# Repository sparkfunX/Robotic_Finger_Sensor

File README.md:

Robotic Finger Sensor 
========================

[*Robotic Finger Sensor (SPX-14200)*](https://www.sparkfun.com/products/14200)  

[*Robotic Finger Sensor v2 (SPX-14687)*](https://www.sparkfun.com/products/14687)

A robotic finger sensor capable of detecting very light touches. Uses the VCNL4040 IR distance sensor. 

Repository Contents
------------------

* **/Firmware** - Example Arduino sketch to demostrate how to read from the various sensors.
* **/Hardware** - All the Eagle PCB design files (.brd, .sch). MOld files are included as well. 

License Information
-------------------

This product is _**open source**_! 

Please review the LICENSE.md file for license information. 

If you have any questions or concerns on licensing, please contact technical support on our [SparkFun forums](https://forum.sparkfun.com/viewforum.php?f=152).

Distributed as-is; no warranty is given.

- Your friends at SparkFun.

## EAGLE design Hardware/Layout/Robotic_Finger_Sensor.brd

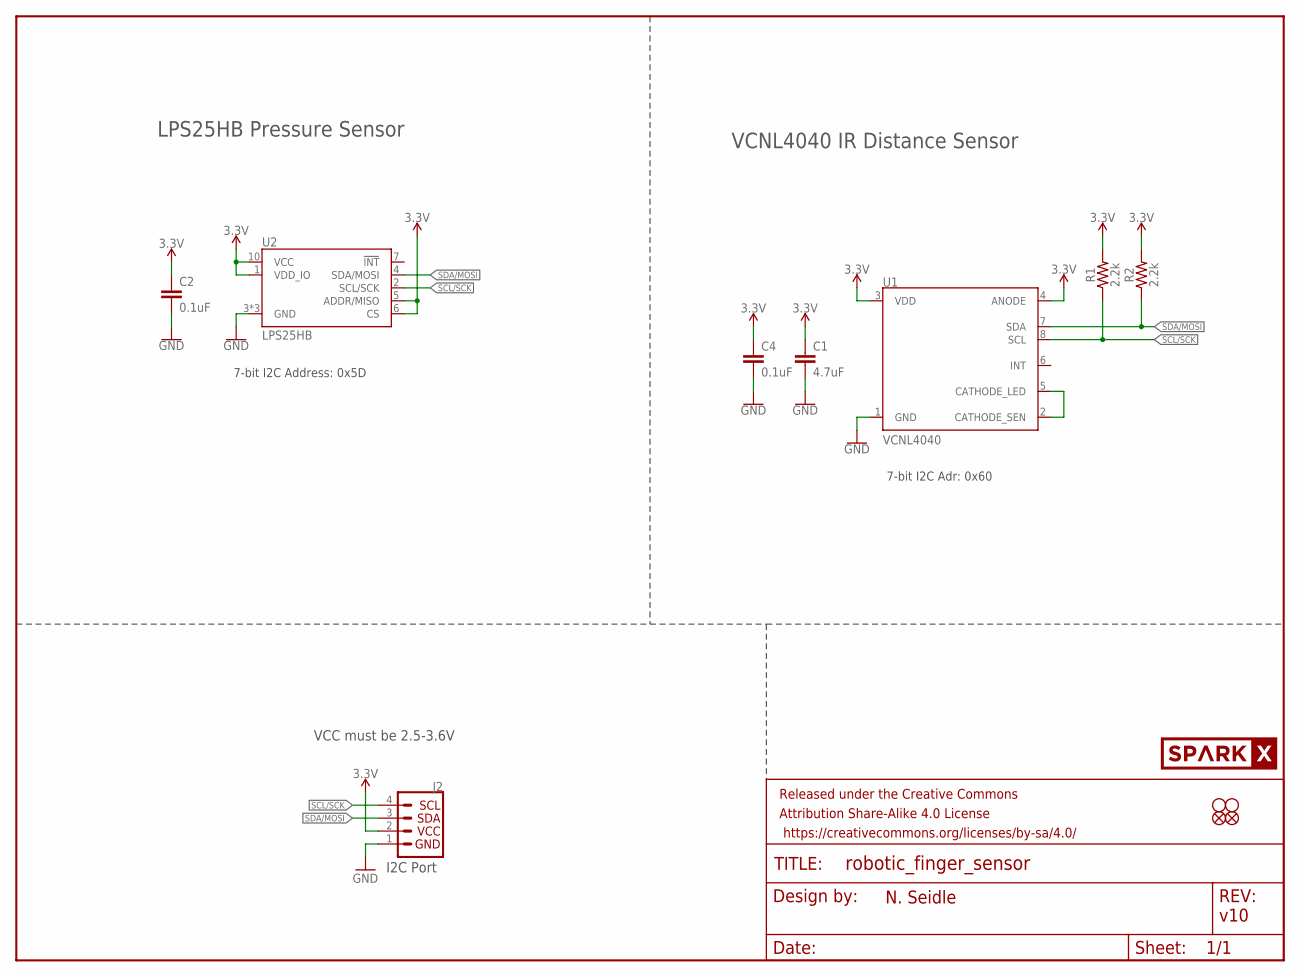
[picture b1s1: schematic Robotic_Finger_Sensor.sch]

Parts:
C1: 4.7uF; 0603
C2, C4: 0.1uF; 0603
FD1, FD2: FIDUCIALUFIDUCIAL; FIDUCIAL-MICRO
FRAME2: FRAME-LETTER; CREATIVE_COMMONS
J2: I2C_STANDARDJS-1MM; 1X04_1MM_RA
R1, R2: 2.2k; 0603
U1: VCNL4040
U2: LPS25HB
U$2: SPARKX-LOGO3; SPARKX-SMALL
U$3, U$4: STAND-OFF; STAND-OFF-#2

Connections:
3.3V: C1.1, C2.1, C4.1, J2.2 (VCC), R1.2, R2.2, U1.3 (VDD), U1.4 (ANODE), U2.1 (VDD_IO), U2.5 (ADDR/MISO), U2.6 (CS), U2.10 (VCC)
GND: C1.2, C2.2, C4.2, J2.1 (GND), U1.1 (GND), U2.3 (GND), U2.8 (GND), U2.9 (GND)
unnamed: U1.2 (CATHODE_SEN), U1.5 (CATHODE_LED)
SCL/SCK: J2.4 (SCL), R1.1, U1.8 (SCL), U2.2 (SCL/SCK)
SDA/MOSI: J2.3 (SDA), R2.1, U1.7 (SDA), U2.4 (SDA/MOSI)

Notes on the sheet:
v10
N. Seidle
VCNL4040 IR Distance Sensor
VCC must be 2.5-3.6V
I2C Port
7-bit I2C Adr: 0x60
LPS25HB Pressure Sensor
7-bit I2C Address: 0x5D

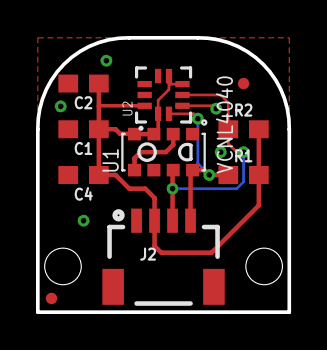
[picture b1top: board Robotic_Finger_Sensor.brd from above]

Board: 2 copper layers, 14.0 x 15.2 mm, 18 parts (5 on the bottom side), 5 nets.

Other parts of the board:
U$6: ROBOTIC0
U$7: SENSOR2
U$9: FINGER0
U$11: (QWIIC)

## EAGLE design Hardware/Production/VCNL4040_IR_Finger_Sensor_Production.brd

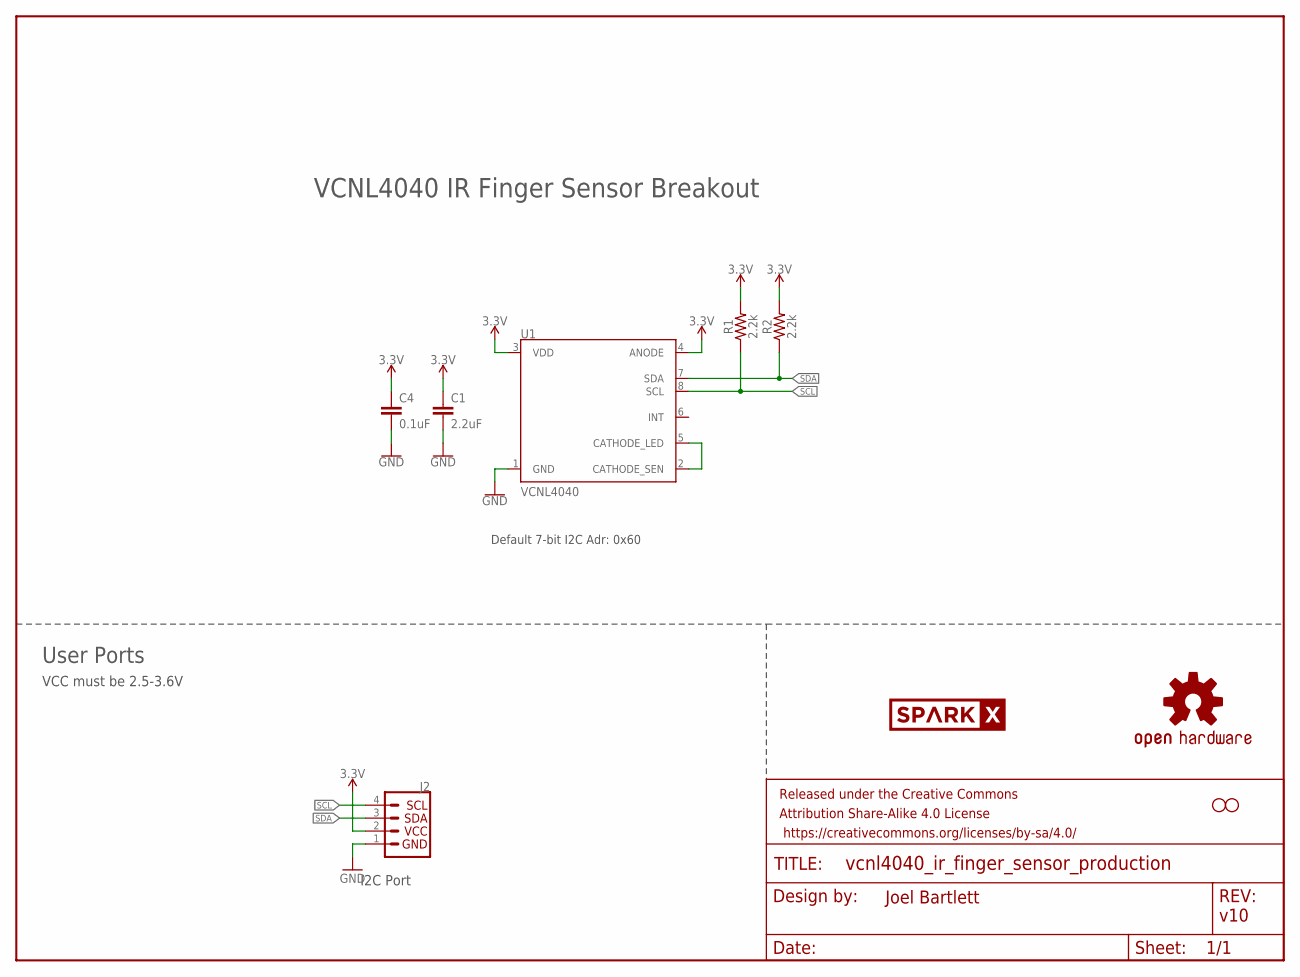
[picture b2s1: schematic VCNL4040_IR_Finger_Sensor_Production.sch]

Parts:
C1: 2.2uF; 0603
C4: 0.1uF; 0603
FRAME2: FRAME-LETTER; CREATIVE_COMMONS
J2: I2C_STANDARDJS-1MM; 1X04_1MM_RA
R1, R2: 2.2k; 0603
U1: VCNL4040
U$1: OSHW-LOGOS; OSHW-LOGO-S
U$2: SPARKX-LOGO3; SPARKX-SMALL
U$3, U$4: STAND-OFF; STAND-OFF-#2

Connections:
3.3V: C1.1, C4.1, J2.2 (VCC), R1.2, R2.2, U1.3 (VDD), U1.4 (ANODE)
GND: C1.2, C4.2, J2.1 (GND), U1.1 (GND)
unnamed: U1.2 (CATHODE_SEN), U1.5 (CATHODE_LED)
SCL: J2.4 (SCL), R1.1, U1.8 (SCL)
SDA: J2.3 (SDA), R2.1, U1.7 (SDA)

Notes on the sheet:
v10
Joel Bartlett
VCNL4040 IR Finger Sensor Breakout
User Ports
VCC must be 2.5-3.6V
I2C Port
Default 7-bit I2C Adr: 0x60

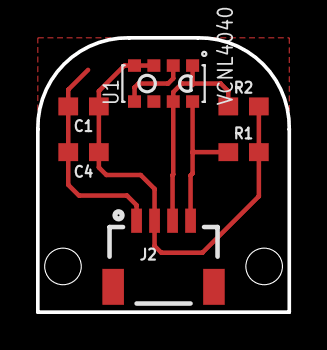
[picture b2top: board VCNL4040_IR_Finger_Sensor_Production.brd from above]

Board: 2 copper layers, 14.0 x 15.2 mm, 11 parts (2 on the bottom side), 5 nets.

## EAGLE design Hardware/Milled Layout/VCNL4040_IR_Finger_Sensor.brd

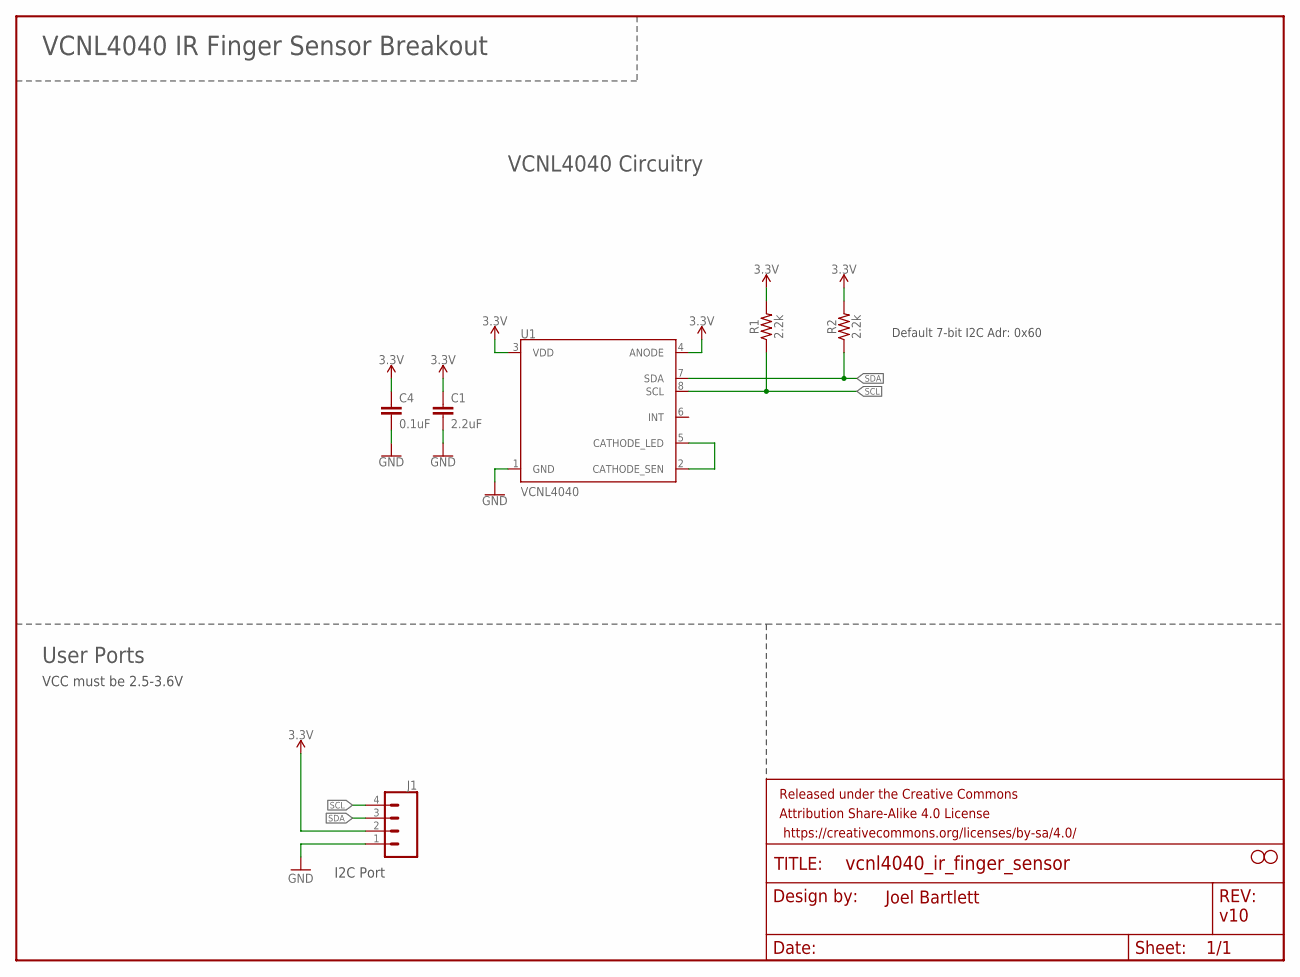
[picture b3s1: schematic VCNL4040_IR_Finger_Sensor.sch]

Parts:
C1: 2.2uF; 0603
C4: 0.1uF; 0603
FRAME2: FRAME-LETTER; CREATIVE_COMMONS
J1: CONN_04SMD2; 1X04_1MM_RA
R1, R2: 2.2k; 0603
U1: VCNL4040
U$1, U$2: STAND-OFF; STAND-OFF-#2

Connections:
3.3V: C1.1, C4.1, J1.2, R1.2, R2.2, U1.3 (VDD), U1.4 (ANODE)
GND: C1.2, C4.2, J1.1, U1.1 (GND)
unnamed: U1.2 (CATHODE_SEN), U1.5 (CATHODE_LED)
SCL: J1.4, R1.1, U1.8 (SCL)
SDA: J1.3, R2.1, U1.7 (SDA)

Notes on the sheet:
v10
Joel Bartlett
VCNL4040 IR Finger Sensor Breakout
VCNL4040 Circuitry
User Ports
VCC must be 2.5-3.6V
I2C Port
Default 7-bit I2C Adr: 0x60

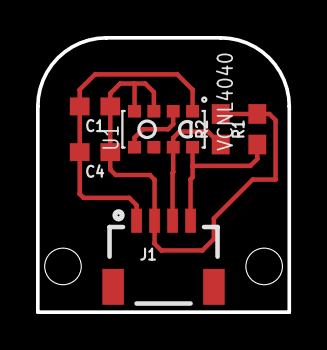
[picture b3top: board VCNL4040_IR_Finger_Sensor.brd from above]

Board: 2 copper layers, 14.0 x 15.2 mm, 9 parts (0 on the bottom side), 5 nets.

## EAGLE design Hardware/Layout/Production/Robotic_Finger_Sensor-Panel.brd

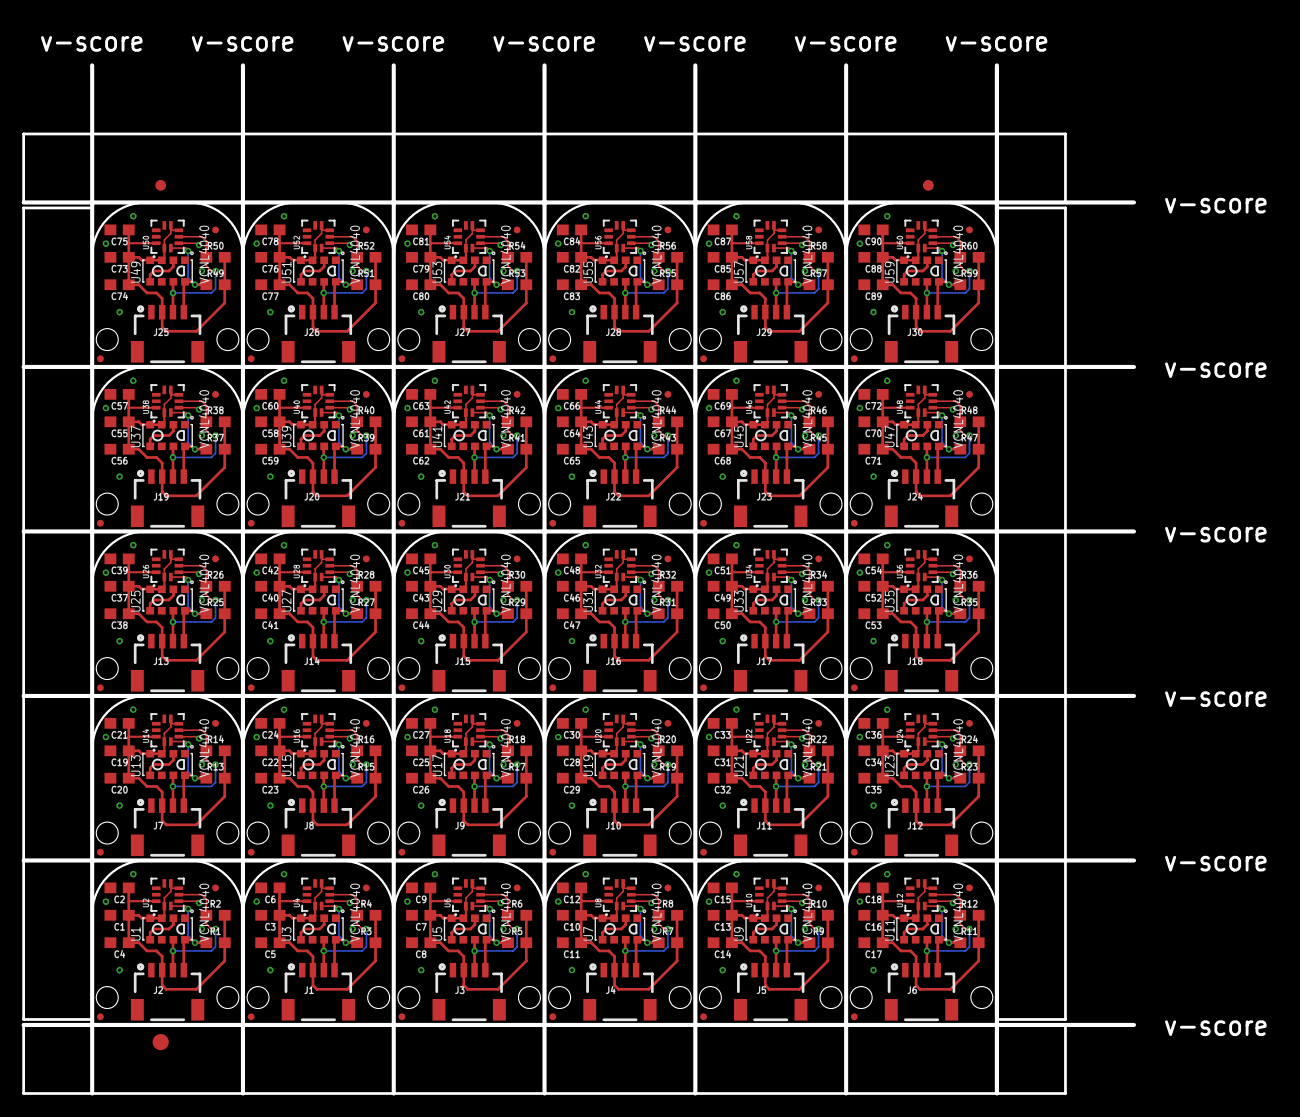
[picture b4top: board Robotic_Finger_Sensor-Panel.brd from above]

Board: 2 copper layers, 116.1 x 99.1 mm, 513 parts (150 on the bottom side), 150 nets.

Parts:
C1, C3, C7, C10, C13, C16, C19, C22, C25, C28, C31, C34, C37, C40, C43, C46, C49, C52, C55, C58, C61, C64, C67, C70, C73, C76, C79, C82, C85, C88: 4.7uF; 0603
C2, C4, C5, C6, C8, C9, C11, C12, C14, C15, C17, C18, C20, C21, C23, C24, C26, C27, C29, C30, C32, C33, C35, C36, C38, C39, C41, C42, C44, C45, C47, C48, C50, C51, C53, C54, C56, C57, C59, C60, C62, C63, C65, C66, C68, C69, C71, C72, C74, C75, C77, C78, C80, C81, C83, C84, C86, C87, C89, C90: 0.1uF; 0603
E$1, E$2: FIDUCIAL-1X2
E$3: FIDUCIAL-1.5X3
FD1, FD2, FD3, FD4, FD5, FD6, FD7, FD8, FD9, FD10, FD11, FD12, FD13, FD14, FD15, FD16, FD17, FD18, FD19, FD20, FD21, FD22, FD23, FD24, FD25, FD26, FD27, FD28, FD29, FD30, FD31, FD32, FD33, FD34, FD35, FD36, FD37, FD38, FD39, FD40, FD41, FD42, FD43, FD44, FD45, FD46, FD47, FD48, FD49, FD50, FD51, FD52, FD53, FD54, FD55, FD56, FD57, FD58, FD59, FD60: FIDUCIALUFIDUCIAL; FIDUCIAL-MICRO
J1, J2, J3, J4, J5, J6, J7, J8, J9, J10, J11, J12, J13, J14, J15, J16, J17, J18, J19, J20, J21, J22, J23, J24, J25, J26, J27, J28, J29, J30: 1X04_1MM_RA
R1, R2, R3, R4, R5, R6, R7, R8, R9, R10, R11, R12, R13, R14, R15, R16, R17, R18, R19, R20, R21, R22, R23, R24, R25, R26, R27, R28, R29, R30, R31, R32, R33, R34, R35, R36, R37, R38, R39, R40, R41, R42, R43, R44, R45, R46, R47, R48, R49, R50, R51, R52, R53, R54, R55, R56, R57, R58, R59, R60: 2.2k; 0603
U1, U3, U5, U7, U9, U11, U13, U15, U17, U19, U21, U23, U25, U27, U29, U31, U33, U35, U37, U39, U41, U43, U45, U47, U49, U51, U53, U55, U57, U59: VCNL4040
U2, U4, U6, U8, U10, U12, U14, U16, U18, U20, U22, U24, U26, U28, U30, U32, U34, U36, U38, U40, U42, U44, U46, U48, U50, U52, U54, U56, U58, U60: LPS25HB
U$1, U$2, U$15, U$22, U$29, U$36, U$43, U$50, U$57, U$64, U$71, U$78, U$85, U$92, U$99, U$106, U$113, U$120, U$127, U$134, U$141, U$148, U$155, U$162, U$169, U$176, U$183, U$190, U$197, U$204: SPARKX-LOGO3; SPARKX-SMALL
U$3, U$4, U$5, U$8, U$16, U$17, U$23, U$24, U$30, U$31, U$37, U$38, U$44, U$45, U$51, U$52, U$58, U$59, U$65, U$66, U$72, U$73, U$79, U$80, U$86, U$87, U$93, U$94, U$100, U$101, U$107, U$108, U$114, U$115, U$121, U$122, U$128, U$129, U$135, U$136, U$142, U$143, U$149, U$150, U$156, U$157, U$163, U$164, U$170, U$171, U$177, U$178, U$184, U$185, U$191, U$192, U$198, U$199, U$205, U$206: STAND-OFF; STAND-OFF-#2
U$6, U$12, U$19, U$26, U$33, U$40, U$47, U$54, U$61, U$68, U$75, U$82, U$89, U$96, U$103, U$110, U$117, U$124, U$131, U$138, U$145, U$152, U$159, U$166, U$173, U$180, U$187, U$194, U$201, U$208: ROBOTIC0
U$7, U$13, U$20, U$27, U$34, U$41, U$48, U$55, U$62, U$69, U$76, U$83, U$90, U$97, U$104, U$111, U$118, U$125, U$132, U$139, U$146, U$153, U$160, U$167, U$174, U$181, U$188, U$195, U$202, U$209: SENSOR2
U$9, U$14, U$21, U$28, U$35, U$42, U$49, U$56, U$63, U$70, U$77, U$84, U$91, U$98, U$105, U$112, U$119, U$126, U$133, U$140, U$147, U$154, U$161, U$168, U$175, U$182, U$189, U$196, U$203, U$210: FINGER0
U$10, U$11, U$18, U$25, U$32, U$39, U$46, U$53, U$60, U$67, U$74, U$81, U$88, U$95, U$102, U$109, U$116, U$123, U$130, U$137, U$144, U$151, U$158, U$165, U$172, U$179, U$186, U$193, U$200, U$207: (QWIIC)

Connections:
3.3V: C1.1, C2.1, C4.1, J2.2, R1.2, R2.2, U1.3, U1.4, U2.1, U2.5, U2.6, U2.10
3.3V1: C3.1, C5.1, C6.1, J1.2, R3.2, R4.2, U3.3, U3.4, U4.1, U4.5, U4.6, U4.10
3.3V2: C7.1, C8.1, C9.1, J3.2, R5.2, R6.2, U5.3, U5.4, U6.1, U6.5, U6.6, U6.10
3.3V3: C10.1, C11.1, C12.1, J4.2, R7.2, R8.2, U7.3, U7.4, U8.1, U8.5, U8.6, U8.10
3.3V4: C13.1, C14.1, C15.1, J5.2, R9.2, R10.2, U9.3, U9.4, U10.1, U10.5, U10.6, U10.10
3.3V5: C16.1, C17.1, C18.1, J6.2, R11.2, R12.2, U11.3, U11.4, U12.1, U12.5, U12.6, U12.10
3.3V6: C19.1, C20.1, C21.1, J7.2, R13.2, R14.2, U13.3, U13.4, U14.1, U14.5, U14.6, U14.10
3.3V7: C22.1, C23.1, C24.1, J8.2, R15.2, R16.2, U15.3, U15.4, U16.1, U16.5, U16.6, U16.10
3.3V8: C25.1, C26.1, C27.1, J9.2, R17.2, R18.2, U17.3, U17.4, U18.1, U18.5, U18.6, U18.10
3.3V9: C28.1, C29.1, C30.1, J10.2, R19.2, R20.2, U19.3, U19.4, U20.1, U20.5, U20.6, U20.10
3.3V10: C31.1, C32.1, C33.1, J11.2, R21.2, R22.2, U21.3, U21.4, U22.1, U22.5, U22.6, U22.10
3.3V11: C34.1, C35.1, C36.1, J12.2, R23.2, R24.2, U23.3, U23.4, U24.1, U24.5, U24.6, U24.10
3.3V12: C37.1, C38.1, C39.1, J13.2, R25.2, R26.2, U25.3, U25.4, U26.1, U26.5, U26.6, U26.10
3.3V13: C40.1, C41.1, C42.1, J14.2, R27.2, R28.2, U27.3, U27.4, U28.1, U28.5, U28.6, U28.10
3.3V14: C43.1, C44.1, C45.1, J15.2, R29.2, R30.2, U29.3, U29.4, U30.1, U30.5, U30.6, U30.10
3.3V15: C46.1, C47.1, C48.1, J16.2, R31.2, R32.2, U31.3, U31.4, U32.1, U32.5, U32.6, U32.10
3.3V16: C49.1, C50.1, C51.1, J17.2, R33.2, R34.2, U33.3, U33.4, U34.1, U34.5, U34.6, U34.10
3.3V17: C52.1, C53.1, C54.1, J18.2, R35.2, R36.2, U35.3, U35.4, U36.1, U36.5, U36.6, U36.10
3.3V18: C55.1, C56.1, C57.1, J19.2, R37.2, R38.2, U37.3, U37.4, U38.1, U38.5, U38.6, U38.10
3.3V19: C58.1, C59.1, C60.1, J20.2, R39.2, R40.2, U39.3, U39.4, U40.1, U40.5, U40.6, U40.10
3.3V20: C61.1, C62.1, C63.1, J21.2, R41.2, R42.2, U41.3, U41.4, U42.1, U42.5, U42.6, U42.10
3.3V21: C64.1, C65.1, C66.1, J22.2, R43.2, R44.2, U43.3, U43.4, U44.1, U44.5, U44.6, U44.10
3.3V22: C67.1, C68.1, C69.1, J23.2, R45.2, R46.2, U45.3, U45.4, U46.1, U46.5, U46.6, U46.10
3.3V23: C70.1, C71.1, C72.1, J24.2, R47.2, R48.2, U47.3, U47.4, U48.1, U48.5, U48.6, U48.10
3.3V24: C73.1, C74.1, C75.1, J25.2, R49.2, R50.2, U49.3, U49.4, U50.1, U50.5, U50.6, U50.10
3.3V25: C76.1, C77.1, C78.1, J26.2, R51.2, R52.2, U51.3, U51.4, U52.1, U52.5, U52.6, U52.10
3.3V26: C79.1, C80.1, C81.1, J27.2, R53.2, R54.2, U53.3, U53.4, U54.1, U54.5, U54.6, U54.10
3.3V27: C82.1, C83.1, C84.1, J28.2, R55.2, R56.2, U55.3, U55.4, U56.1, U56.5, U56.6, U56.10
3.3V28: C85.1, C86.1, C87.1, J29.2, R57.2, R58.2, U57.3, U57.4, U58.1, U58.5, U58.6, U58.10
3.3V29: C88.1, C89.1, C90.1, J30.2, R59.2, R60.2, U59.3, U59.4, U60.1, U60.5, U60.6, U60.10
GND: C1.2, C2.2, C4.2, J2.1, U1.1, U2.3, U2.8, U2.9
GND1: C3.2, C5.2, C6.2, J1.1, U3.1, U4.3, U4.8, U4.9
GND2: C7.2, C8.2, C9.2, J3.1, U5.1, U6.3, U6.8, U6.9
GND3: C10.2, C11.2, C12.2, J4.1, U7.1, U8.3, U8.8, U8.9
GND4: C13.2, C14.2, C15.2, J5.1, U9.1, U10.3, U10.8, U10.9
GND5: C16.2, C17.2, C18.2, J6.1, U11.1, U12.3, U12.8, U12.9
GND6: C19.2, C20.2, C21.2, J7.1, U13.1, U14.3, U14.8, U14.9
GND7: C22.2, C23.2, C24.2, J8.1, U15.1, U16.3, U16.8, U16.9
GND8: C25.2, C26.2, C27.2, J9.1, U17.1, U18.3, U18.8, U18.9
GND9: C28.2, C29.2, C30.2, J10.1, U19.1, U20.3, U20.8, U20.9
GND10: C31.2, C32.2, C33.2, J11.1, U21.1, U22.3, U22.8, U22.9
GND11: C34.2, C35.2, C36.2, J12.1, U23.1, U24.3, U24.8, U24.9
GND12: C37.2, C38.2, C39.2, J13.1, U25.1, U26.3, U26.8, U26.9
GND13: C40.2, C41.2, C42.2, J14.1, U27.1, U28.3, U28.8, U28.9
GND14: C43.2, C44.2, C45.2, J15.1, U29.1, U30.3, U30.8, U30.9
GND15: C46.2, C47.2, C48.2, J16.1, U31.1, U32.3, U32.8, U32.9
GND16: C49.2, C50.2, C51.2, J17.1, U33.1, U34.3, U34.8, U34.9
GND17: C52.2, C53.2, C54.2, J18.1, U35.1, U36.3, U36.8, U36.9
GND18: C55.2, C56.2, C57.2, J19.1, U37.1, U38.3, U38.8, U38.9
GND19: C58.2, C59.2, C60.2, J20.1, U39.1, U40.3, U40.8, U40.9
GND20: C61.2, C62.2, C63.2, J21.1, U41.1, U42.3, U42.8, U42.9
GND21: C64.2, C65.2, C66.2, J22.1, U43.1, U44.3, U44.8, U44.9
GND22: C67.2, C68.2, C69.2, J23.1, U45.1, U46.3, U46.8, U46.9
GND23: C70.2, C71.2, C72.2, J24.1, U47.1, U48.3, U48.8, U48.9
GND24: C73.2, C74.2, C75.2, J25.1, U49.1, U50.3, U50.8, U50.9
GND25: C76.2, C77.2, C78.2, J26.1, U51.1, U52.3, U52.8, U52.9
GND26: C79.2, C80.2, C81.2, J27.1, U53.1, U54.3, U54.8, U54.9
GND27: C82.2, C83.2, C84.2, J28.1, U55.1, U56.3, U56.8, U56.9
GND28: C85.2, C86.2, C87.2, J29.1, U57.1, U58.3, U58.8, U58.9
GND29: C88.2, C89.2, C90.2, J30.1, U59.1, U60.3, U60.8, U60.9
unnamed: U1.2, U1.5
unnamed: U3.2, U3.5
unnamed: U5.2, U5.5
unnamed: U7.2, U7.5
unnamed: U9.2, U9.5
unnamed: U11.2, U11.5
unnamed: U13.2, U13.5
unnamed: U15.2, U15.5
unnamed: U17.2, U17.5
unnamed: U19.2, U19.5
unnamed: U21.2, U21.5
unnamed: U23.2, U23.5
unnamed: U25.2, U25.5
unnamed: U27.2, U27.5
unnamed: U29.2, U29.5
unnamed: U31.2, U31.5
unnamed: U33.2, U33.5
unnamed: U35.2, U35.5
unnamed: U37.2, U37.5
unnamed: U39.2, U39.5
unnamed: U41.2, U41.5
unnamed: U43.2, U43.5
unnamed: U45.2, U45.5
unnamed: U47.2, U47.5
unnamed: U49.2, U49.5
unnamed: U51.2, U51.5
unnamed: U53.2, U53.5
unnamed: U55.2, U55.5
unnamed: U57.2, U57.5
unnamed: U59.2, U59.5
SCL/SCK: J2.4, R1.1, U1.8, U2.2
SCL/SCK1: J1.4, R3.1, U3.8, U4.2
SCL/SCK2: J3.4, R5.1, U5.8, U6.2
SCL/SCK3: J4.4, R7.1, U7.8, U8.2
SCL/SCK4: J5.4, R9.1, U9.8, U10.2
SCL/SCK5: J6.4, R11.1, U11.8, U12.2
SCL/SCK6: J7.4, R13.1, U13.8, U14.2
SCL/SCK7: J8.4, R15.1, U15.8, U16.2
SCL/SCK8: J9.4, R17.1, U17.8, U18.2
SCL/SCK9: J10.4, R19.1, U19.8, U20.2
SCL/SCK10: J11.4, R21.1, U21.8, U22.2
SCL/SCK11: J12.4, R23.1, U23.8, U24.2
SCL/SCK12: J13.4, R25.1, U25.8, U26.2
SCL/SCK13: J14.4, R27.1, U27.8, U28.2
SCL/SCK14: J15.4, R29.1, U29.8, U30.2
SCL/SCK15: J16.4, R31.1, U31.8, U32.2
SCL/SCK16: J17.4, R33.1, U33.8, U34.2
SCL/SCK17: J18.4, R35.1, U35.8, U36.2
SCL/SCK18: J19.4, R37.1, U37.8, U38.2
SCL/SCK19: J20.4, R39.1, U39.8, U40.2
SCL/SCK20: J21.4, R41.1, U41.8, U42.2
SCL/SCK21: J22.4, R43.1, U43.8, U44.2
SCL/SCK22: J23.4, R45.1, U45.8, U46.2
SCL/SCK23: J24.4, R47.1, U47.8, U48.2
SCL/SCK24: J25.4, R49.1, U49.8, U50.2
SCL/SCK25: J26.4, R51.1, U51.8, U52.2
SCL/SCK26: J27.4, R53.1, U53.8, U54.2
SCL/SCK27: J28.4, R55.1, U55.8, U56.2
SCL/SCK28: J29.4, R57.1, U57.8, U58.2
SCL/SCK29: J30.4, R59.1, U59.8, U60.2
SDA/MOSI: J2.3, R2.1, U1.7, U2.4
SDA/MOSI1: J1.3, R4.1, U3.7, U4.4
SDA/MOSI2: J3.3, R6.1, U5.7, U6.4
SDA/MOSI3: J4.3, R8.1, U7.7, U8.4
SDA/MOSI4: J5.3, R10.1, U9.7, U10.4
SDA/MOSI5: J6.3, R12.1, U11.7, U12.4
SDA/MOSI6: J7.3, R14.1, U13.7, U14.4
SDA/MOSI7: J8.3, R16.1, U15.7, U16.4
SDA/MOSI8: J9.3, R18.1, U17.7, U18.4
SDA/MOSI9: J10.3, R20.1, U19.7, U20.4
SDA/MOSI10: J11.3, R22.1, U21.7, U22.4
SDA/MOSI11: J12.3, R24.1, U23.7, U24.4
SDA/MOSI12: J13.3, R26.1, U25.7, U26.4
SDA/MOSI13: J14.3, R28.1, U27.7, U28.4
SDA/MOSI14: J15.3, R30.1, U29.7, U30.4
SDA/MOSI15: J16.3, R32.1, U31.7, U32.4
SDA/MOSI16: J17.3, R34.1, U33.7, U34.4
SDA/MOSI17: J18.3, R36.1, U35.7, U36.4
SDA/MOSI18: J19.3, R38.1, U37.7, U38.4
SDA/MOSI19: J20.3, R40.1, U39.7, U40.4
SDA/MOSI20: J21.3, R42.1, U41.7, U42.4
SDA/MOSI21: J22.3, R44.1, U43.7, U44.4
SDA/MOSI22: J23.3, R46.1, U45.7, U46.4
SDA/MOSI23: J24.3, R48.1, U47.7, U48.4
SDA/MOSI24: J25.3, R50.1, U49.7, U50.4
SDA/MOSI25: J26.3, R52.1, U51.7, U52.4
SDA/MOSI26: J27.3, R54.1, U53.7, U54.4
SDA/MOSI27: J28.3, R56.1, U55.7, U56.4
SDA/MOSI28: J29.3, R58.1, U57.7, U58.4
SDA/MOSI29: J30.3, R60.1, U59.7, U60.4

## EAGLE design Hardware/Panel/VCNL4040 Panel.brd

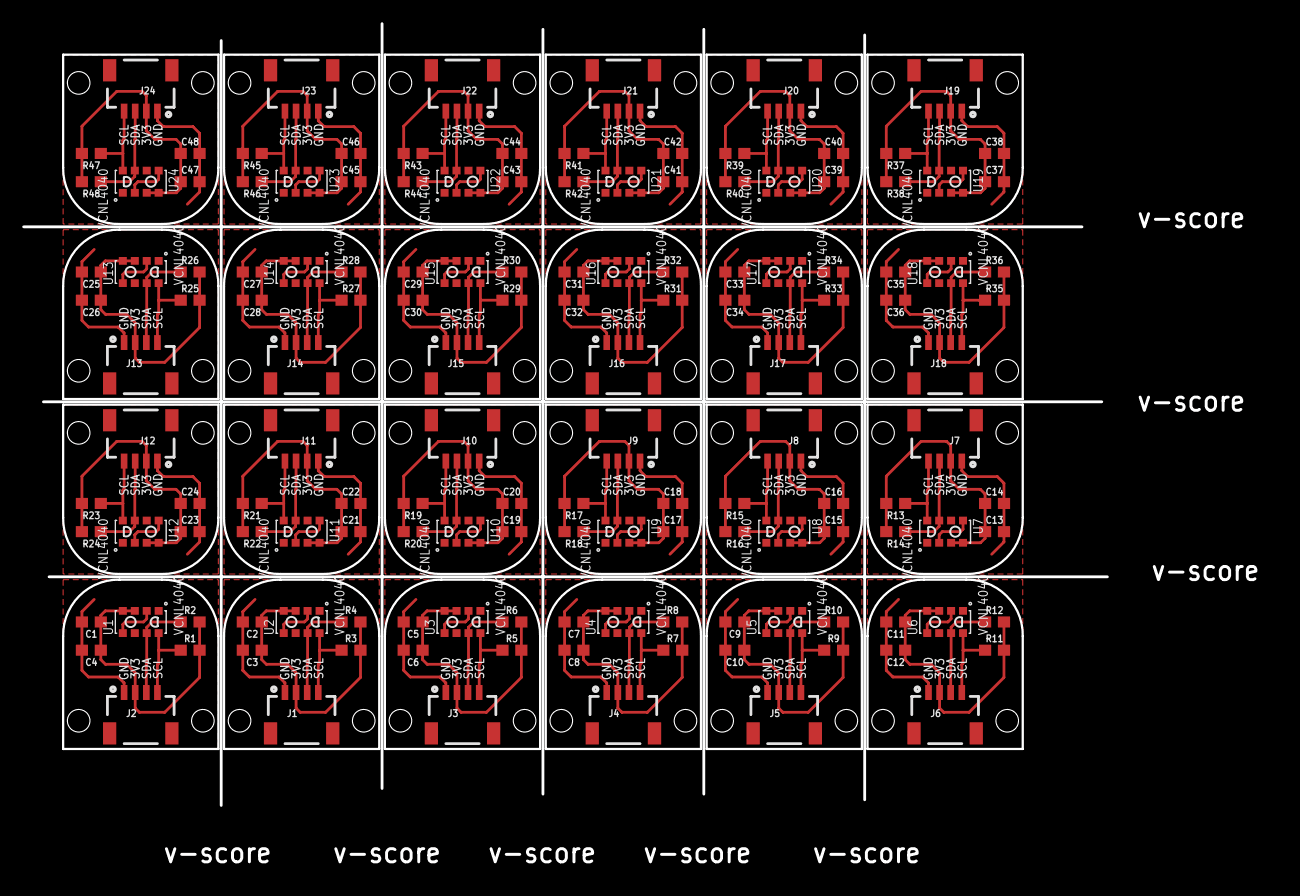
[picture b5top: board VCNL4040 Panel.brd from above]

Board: 2 copper layers, 112.7 x 76.4 mm, 240 parts (48 on the bottom side), 120 nets.

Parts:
C1, C2, C5, C7, C9, C11, C13, C15, C17, C19, C21, C23, C25, C27, C29, C31, C33, C35, C37, C39, C41, C43, C45, C47: 2.2uF; 0603
C3, C4, C6, C8, C10, C12, C14, C16, C18, C20, C22, C24, C26, C28, C30, C32, C34, C36, C38, C40, C42, C44, C46, C48: 0.1uF; 0603
J1, J2, J3, J4, J5, J6, J7, J8, J9, J10, J11, J12, J13, J14, J15, J16, J17, J18, J19, J20, J21, J22, J23, J24: 1X04_1MM_RA
R1, R2, R3, R4, R5, R6, R7, R8, R9, R10, R11, R12, R13, R14, R15, R16, R17, R18, R19, R20, R21, R22, R23, R24, R25, R26, R27, R28, R29, R30, R31, R32, R33, R34, R35, R36, R37, R38, R39, R40, R41, R42, R43, R44, R45, R46, R47, R48: 2.2k; 0603
U1, U2, U3, U4, U5, U6, U7, U8, U9, U10, U11, U12, U13, U14, U15, U16, U17, U18, U19, U20, U21, U22, U23, U24: VCNL4040
U$1, U$5, U$9, U$13, U$17, U$21, U$25, U$29, U$33, U$37, U$41, U$45, U$49, U$53, U$57, U$61, U$65, U$69, U$73, U$77, U$81, U$85, U$89, U$93: OSHW-LOGOS; OSHW-LOGO-S
U$2, U$6, U$10, U$14, U$18, U$22, U$26, U$30, U$34, U$38, U$42, U$46, U$50, U$54, U$58, U$62, U$66, U$70, U$74, U$78, U$82, U$86, U$90, U$94: SPARKX-LOGO3; SPARKX-SMALL
U$3, U$4, U$7, U$8, U$11, U$12, U$15, U$16, U$19, U$20, U$23, U$24, U$27, U$28, U$31, U$32, U$35, U$36, U$39, U$40, U$43, U$44, U$47, U$48, U$51, U$52, U$55, U$56, U$59, U$60, U$63, U$64, U$67, U$68, U$71, U$72, U$75, U$76, U$79, U$80, U$83, U$84, U$87, U$88, U$91, U$92, U$95, U$96: STAND-OFF; STAND-OFF-#2

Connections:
3.3V: C1.1, C4.1, J2.2, R1.2, R2.2, U1.3, U1.4
3.3V1: C2.1, C3.1, J1.2, R3.2, R4.2, U2.3, U2.4
3.3V2: C5.1, C6.1, J3.2, R5.2, R6.2, U3.3, U3.4
3.3V3: C7.1, C8.1, J4.2, R7.2, R8.2, U4.3, U4.4
3.3V4: C9.1, C10.1, J5.2, R9.2, R10.2, U5.3, U5.4
3.3V5: C11.1, C12.1, J6.2, R11.2, R12.2, U6.3, U6.4
3.3V6: C13.1, C14.1, J7.2, R13.2, R14.2, U7.3, U7.4
3.3V7: C15.1, C16.1, J8.2, R15.2, R16.2, U8.3, U8.4
3.3V8: C17.1, C18.1, J9.2, R17.2, R18.2, U9.3, U9.4
3.3V9: C19.1, C20.1, J10.2, R19.2, R20.2, U10.3, U10.4
3.3V10: C21.1, C22.1, J11.2, R21.2, R22.2, U11.3, U11.4
3.3V11: C23.1, C24.1, J12.2, R23.2, R24.2, U12.3, U12.4
3.3V12: C25.1, C26.1, J13.2, R25.2, R26.2, U13.3, U13.4
3.3V13: C27.1, C28.1, J14.2, R27.2, R28.2, U14.3, U14.4
3.3V14: C29.1, C30.1, J15.2, R29.2, R30.2, U15.3, U15.4
3.3V15: C31.1, C32.1, J16.2, R31.2, R32.2, U16.3, U16.4
3.3V16: C33.1, C34.1, J17.2, R33.2, R34.2, U17.3, U17.4
3.3V17: C35.1, C36.1, J18.2, R35.2, R36.2, U18.3, U18.4
3.3V18: C37.1, C38.1, J19.2, R37.2, R38.2, U19.3, U19.4
3.3V19: C39.1, C40.1, J20.2, R39.2, R40.2, U20.3, U20.4
3.3V20: C41.1, C42.1, J21.2, R41.2, R42.2, U21.3, U21.4
3.3V21: C43.1, C44.1, J22.2, R43.2, R44.2, U22.3, U22.4
3.3V22: C45.1, C46.1, J23.2, R45.2, R46.2, U23.3, U23.4
3.3V23: C47.1, C48.1, J24.2, R47.2, R48.2, U24.3, U24.4
GND: C1.2, C4.2, J2.1, U1.1
GND1: C2.2, C3.2, J1.1, U2.1
GND2: C5.2, C6.2, J3.1, U3.1
GND3: C7.2, C8.2, J4.1, U4.1
GND4: C9.2, C10.2, J5.1, U5.1
GND5: C11.2, C12.2, J6.1, U6.1
GND6: C13.2, C14.2, J7.1, U7.1
GND7: C15.2, C16.2, J8.1, U8.1
GND8: C17.2, C18.2, J9.1, U9.1
GND9: C19.2, C20.2, J10.1, U10.1
GND10: C21.2, C22.2, J11.1, U11.1
GND11: C23.2, C24.2, J12.1, U12.1
GND12: C25.2, C26.2, J13.1, U13.1
GND13: C27.2, C28.2, J14.1, U14.1
GND14: C29.2, C30.2, J15.1, U15.1
GND15: C31.2, C32.2, J16.1, U16.1
GND16: C33.2, C34.2, J17.1, U17.1
GND17: C35.2, C36.2, J18.1, U18.1
GND18: C37.2, C38.2, J19.1, U19.1
GND19: C39.2, C40.2, J20.1, U20.1
GND20: C41.2, C42.2, J21.1, U21.1
GND21: C43.2, C44.2, J22.1, U22.1
GND22: C45.2, C46.2, J23.1, U23.1
GND23: C47.2, C48.2, J24.1, U24.1
unnamed: U1.2, U1.5
unnamed: U2.2, U2.5
unnamed: U3.2, U3.5
unnamed: U4.2, U4.5
unnamed: U5.2, U5.5
unnamed: U6.2, U6.5
unnamed: U7.2, U7.5
unnamed: U8.2, U8.5
unnamed: U9.2, U9.5
unnamed: U10.2, U10.5
unnamed: U11.2, U11.5
unnamed: U12.2, U12.5
unnamed: U13.2, U13.5
unnamed: U14.2, U14.5
unnamed: U15.2, U15.5
unnamed: U16.2, U16.5
unnamed: U17.2, U17.5
unnamed: U18.2, U18.5
unnamed: U19.2, U19.5
unnamed: U20.2, U20.5
unnamed: U21.2, U21.5
unnamed: U22.2, U22.5
unnamed: U23.2, U23.5
unnamed: U24.2, U24.5
SCL: J2.4, R1.1, U1.8
SCL1: J1.4, R3.1, U2.8
SCL2: J3.4, R5.1, U3.8
SCL3: J4.4, R7.1, U4.8
SCL4: J5.4, R9.1, U5.8
SCL5: J6.4, R11.1, U6.8
SCL6: J7.4, R13.1, U7.8
SCL7: J8.4, R15.1, U8.8
SCL8: J9.4, R17.1, U9.8
SCL9: J10.4, R19.1, U10.8
SCL10: J11.4, R21.1, U11.8
SCL11: J12.4, R23.1, U12.8
SCL12: J13.4, R25.1, U13.8
SCL13: J14.4, R27.1, U14.8
SCL14: J15.4, R29.1, U15.8
SCL15: J16.4, R31.1, U16.8
SCL16: J17.4, R33.1, U17.8
SCL17: J18.4, R35.1, U18.8
SCL18: J19.4, R37.1, U19.8
SCL19: J20.4, R39.1, U20.8
SCL20: J21.4, R41.1, U21.8
SCL21: J22.4, R43.1, U22.8
SCL22: J23.4, R45.1, U23.8
SCL23: J24.4, R47.1, U24.8
SDA: J2.3, R2.1, U1.7
SDA1: J1.3, R4.1, U2.7
SDA2: J3.3, R6.1, U3.7
SDA3: J4.3, R8.1, U4.7
SDA4: J5.3, R10.1, U5.7
SDA5: J6.3, R12.1, U6.7
SDA6: J7.3, R14.1, U7.7
SDA7: J8.3, R16.1, U8.7
SDA8: J9.3, R18.1, U9.7
SDA9: J10.3, R20.1, U10.7
SDA10: J11.3, R22.1, U11.7
SDA11: J12.3, R24.1, U12.7
SDA12: J13.3, R26.1, U13.7
SDA13: J14.3, R28.1, U14.7
SDA14: J15.3, R30.1, U15.7
SDA15: J16.3, R32.1, U16.7
SDA16: J17.3, R34.1, U17.7
SDA17: J18.3, R36.1, U18.7
SDA18: J19.3, R38.1, U19.7
SDA19: J20.3, R40.1, U20.7
SDA20: J21.3, R42.1, U21.7
SDA21: J22.3, R44.1, U22.7
SDA22: J23.3, R46.1, U23.7
SDA23: J24.3, R48.1, U24.7

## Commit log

2017-02-07 Adding folder structure
2017-02-08 Finished Schematic
2017-02-08 Finished Layout
2017-02-08 Added labels to pins
2017-02-08 Redid Millable version, added Production folder
2017-02-08 Expanded Mill version
2017-02-08 Got rid of INT pin for Mill version
2017-02-08 Moved larger board back to origin
2017-02-08 Added tRestrict under IC
2017-02-08 Trace cleanup
2017-02-08 Expanded bottom dimension to remove via
2017-02-09 New proto layout with no vias
2017-02-15 Adding examples. Testing JST on milled layout.
2017-02-16 Final commit before modifying PCB to match RM's size/shape for molding.
2017-02-27 Added a comparison sketch to make sure new IC works similarly to original.
2017-02-28 Extending PCB for molding
2017-02-28 Moved bed back to origin
2017-02-28 Adding Mold Top PCB designs for mill
2017-02-28 Add 3D files to MOLD folder
2017-02-28 Adding holes to mold PCB
2017-02-28 Modifying main mold
2017-02-28 Changing holes on mold PCB
2017-02-28 Sketchup changes
2017-03-01 Mold update
2017-03-02 Adding Touch example. Adding HDPE mold test.
2017-03-02 Adding production panel
2017-03-03 Adding Production model for mold and PCB topper
2017-03-09 Adding too paths for fine finish 1/16" long reach mold.
2017-03-09 Updating mold for production PCBs
2017-03-09 Adding single version of updated mold.
2017-03-13 Moved IC towards top of PCB to get more in middle of clear overmold.
2017-03-13 Moved IC up to be more in middle of clear overmolding.
2017-03-14 Claw control works pretty well.
2017-03-14 Cleaning up examples
2017-03-14 Adding PDF schematic
2017-03-15 Added single button control to gripper
2017-03-15 Adding pin silk
    Will be covered by encapsulant but may help
2017-03-15 Reduced depth of mold
2017-03-16 Cleanup
2017-04-06 Adding multi-finger examples using PCA9548A
2017-08-30 New panel with silk indicators on pins.
2018-04-02 Adding pressure sensor. Cleaning up repo.
2018-04-02 Modified footprint silk
2018-06-05 Update to LPS25HB pressure sensor
2018-06-12 Updating examples to use modern libraries
2020-02-07 Added test script
2020-02-18 Combine test scripts
2020-02-18 Change status LED to match Uno
2020-02-18 Change tester sketch name
2020-11-20 License and README update
    add new image, and license information

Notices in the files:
parts and their libraries:
SparkFun-Resistors: Licensing: Creative Commons ShareAlike 4.0 International - https://creativecommons.org/licenses/by-sa/4.0
SparkFun-Aesthetics: Released under the Creative Commons Attribution Share-Alike 4.0 License
SparkFun-Aesthetics: https://creativecommons.org/licenses/by-sa/4.0
